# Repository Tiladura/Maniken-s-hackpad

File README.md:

# 6-KEY HACKPAD WITH ENGRAVINGS OF MY CATS NAME
## 2x3 hackpad which can be useful for creating macros or shortcuts for personal use. Convinient key placement, cute cat ascii images and my cats name are engraved(cats name - Tila).
## Features:
- 6 keys 2x3 placement
- xiao rp2040 microcontroller
### Here are my PCB images
| **Schematic** | **PCB** |
|---------------|---------|
||

dont ask why ground output is all the way down there. I don't know

## CAD

Hope you like the simple design! Added ascii cat images and my cats name onto the case :D

## Firmware
You can find firmware files in repo. Compiled it using QMK. To be honest it was such pain in the ass, but it seems to work xd
## Notes
Really liked doing the pcb and cad design! It was really satisfying
## BOM
- 1 SEEEDUINO XIAO RP2040
- 6x DSA Keycaps
- 4x M3x16 Bolt
- 4x M3 Heatset
- 1x case(2 printed parts)

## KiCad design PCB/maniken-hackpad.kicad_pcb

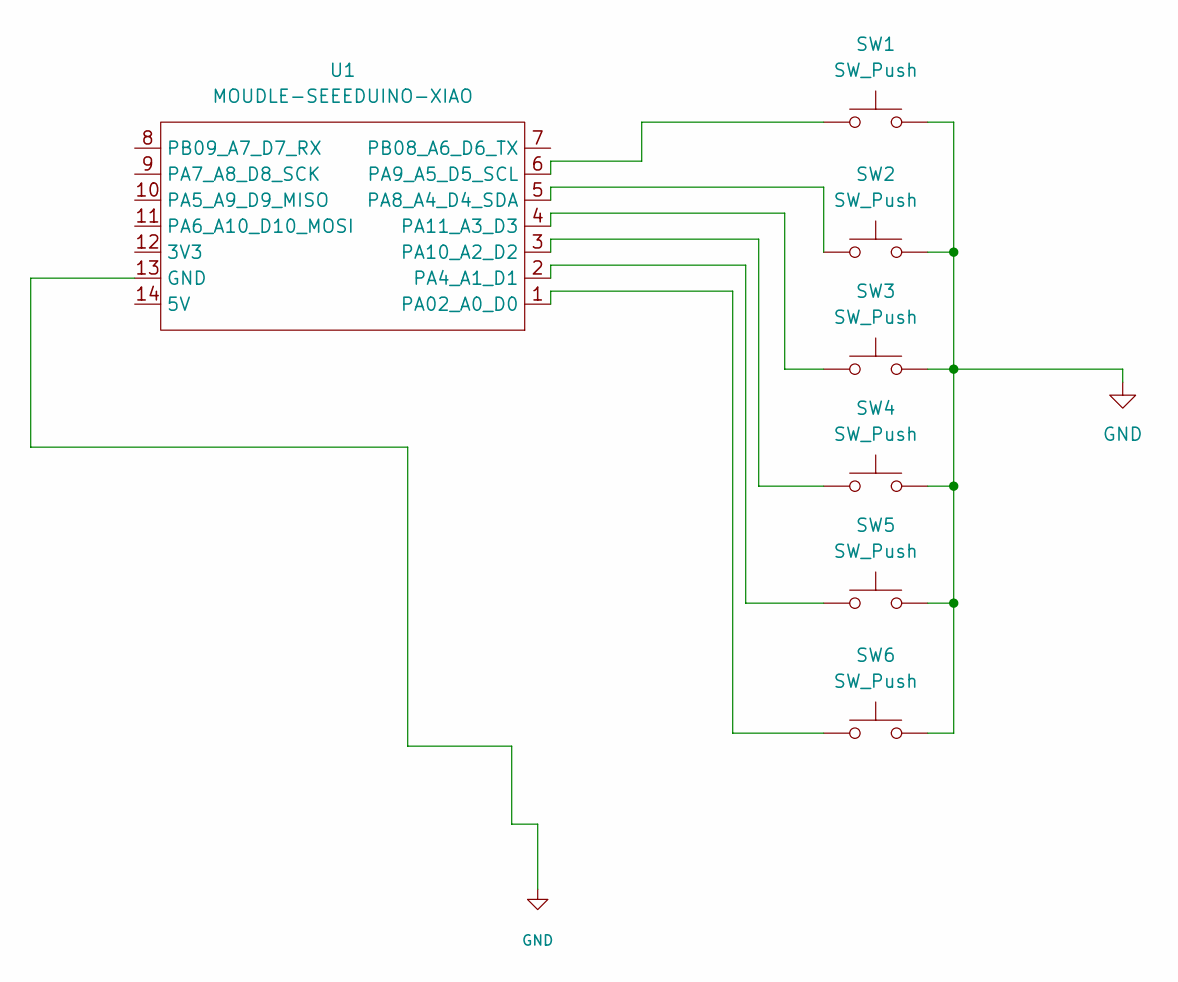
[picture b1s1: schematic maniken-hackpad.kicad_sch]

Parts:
SW1, SW2, SW3, SW4, SW5, SW6: SW_Push; SW_Cherry_MX_1.00u_PCB
U1: MOUDLE-SEEEDUINO-XIAO

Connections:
GND: SW1.2, SW2.2, SW3.2, SW4.2, SW5.2, SW6.2, U1.13 (GND)
unnamed: SW6.1, U1.1 (PA02_A0_D0)
unnamed: SW5.1, U1.2 (PA4_A1_D1)
unnamed: SW2.1, U1.5 (PA8_A4_D4_SDA)
unnamed: SW1.1, U1.6 (PA9_A5_D5_SCL)
unnamed: SW4.1, U1.3 (PA10_A2_D2)
unnamed: SW3.1, U1.4 (PA11_A3_D3)

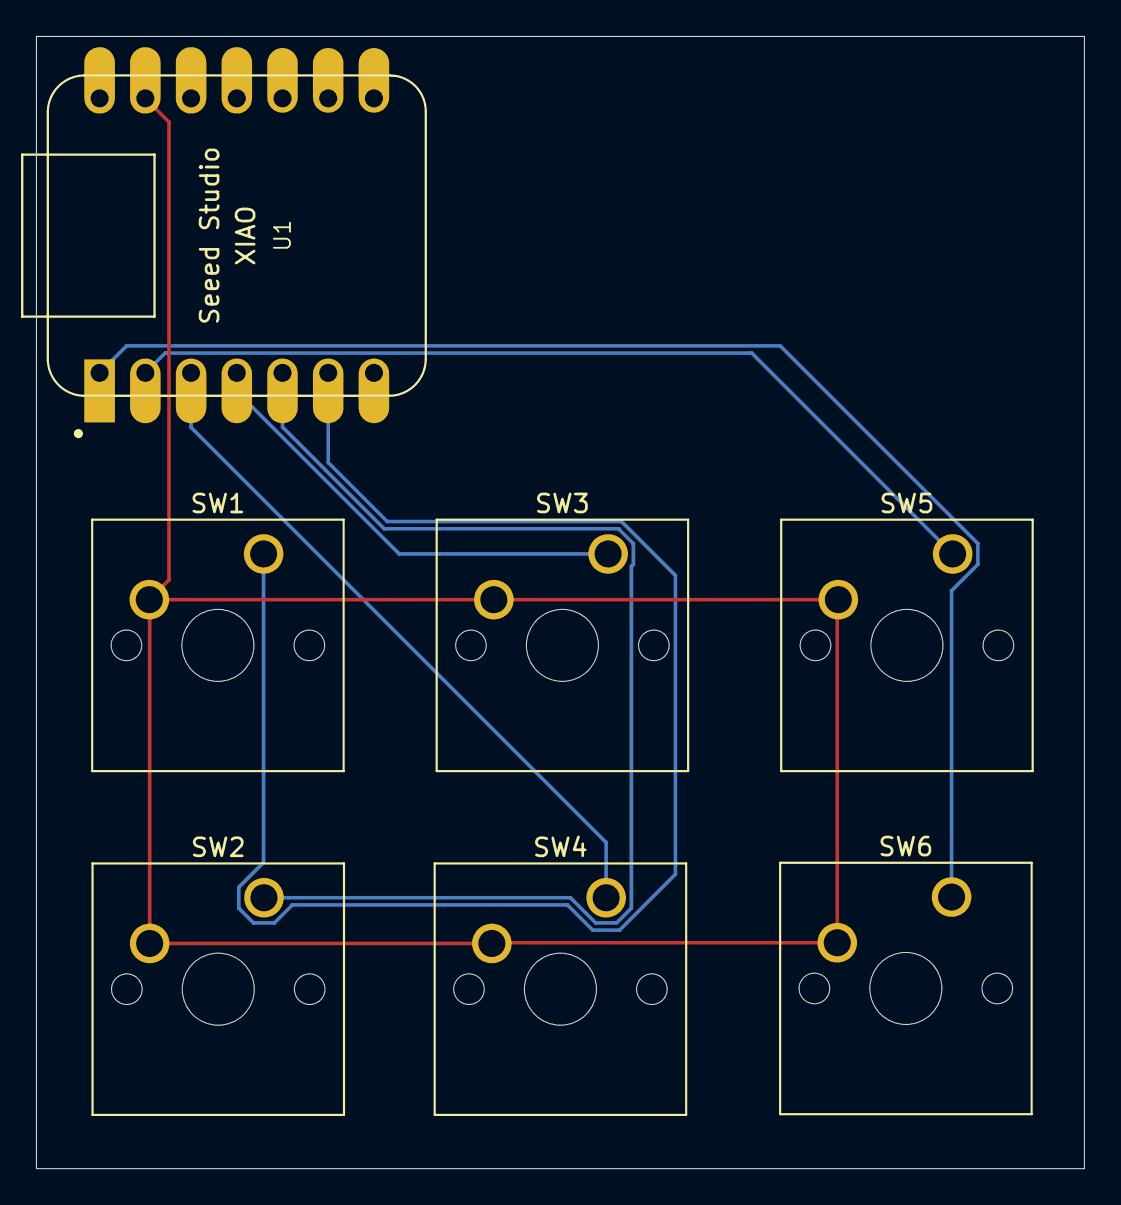
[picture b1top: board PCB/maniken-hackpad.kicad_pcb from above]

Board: 2 copper layers, 58.2 x 62.9 mm, 7 parts (0 on the bottom side), 7 nets.

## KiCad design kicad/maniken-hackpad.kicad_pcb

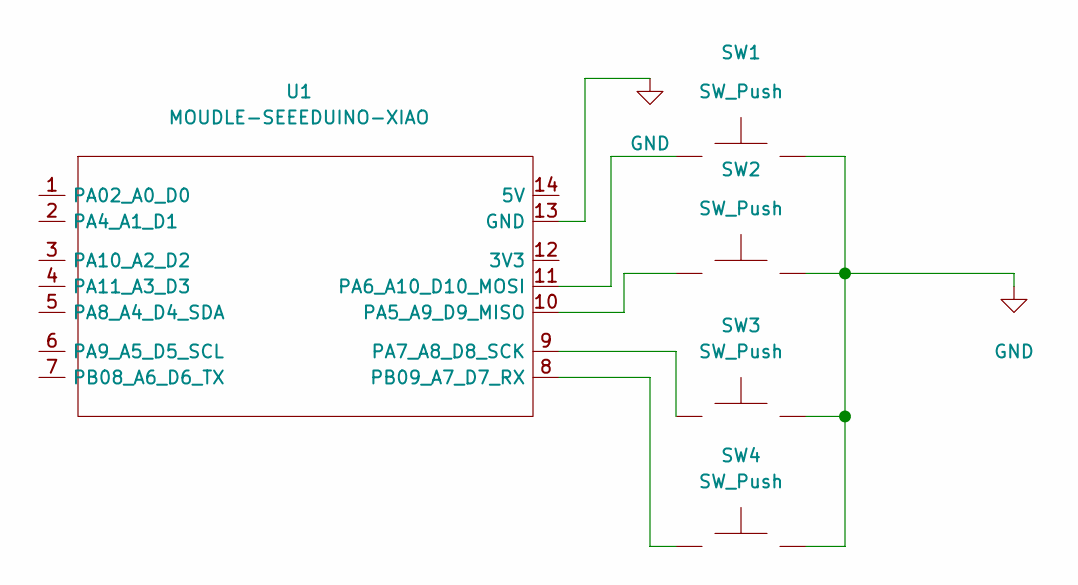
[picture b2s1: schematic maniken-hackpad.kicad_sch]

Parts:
SW1, SW2, SW3, SW4: SW_Push; SW_Cherry_MX_1.00u_PCB
U1: MOUDLE-SEEEDUINO-XIAO; XIAO-Generic-Hybrid-14P-2.54-21X17.8MM

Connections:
GND: SW1.2, SW2.2, SW3.2, SW4.2, U1.13 (GND)
unnamed: SW2.1, U1.10 (PA5_A9_D9_MISO)
unnamed: SW1.1, U1.11 (PA6_A10_D10_MOSI)
unnamed: SW3.1, U1.9 (PA7_A8_D8_SCK)
unnamed: SW4.1, U1.8 (PB09_A7_D7_RX)

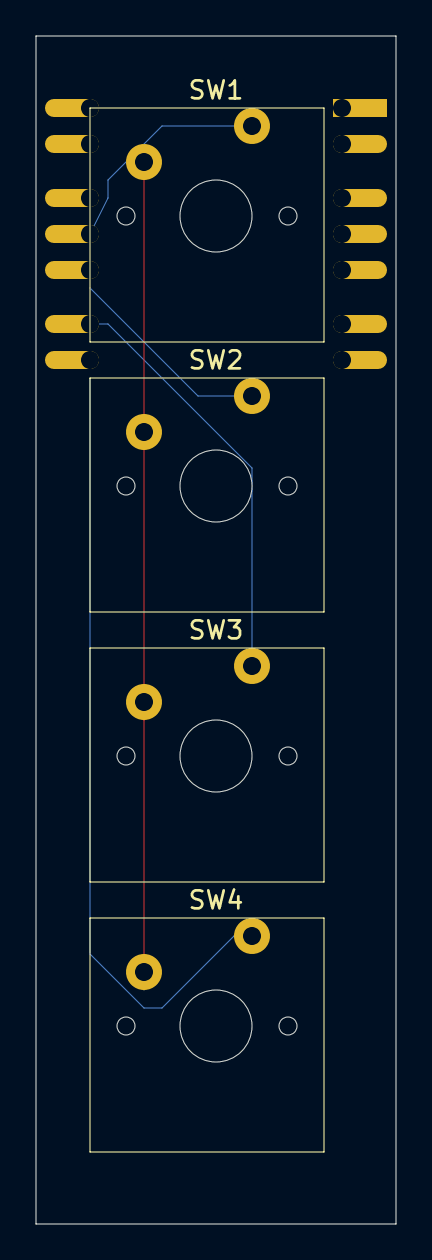
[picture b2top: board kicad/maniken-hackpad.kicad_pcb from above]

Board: 2 copper layers, 20.0 x 66.0 mm, 5 parts (1 on the bottom side), 5 nets.

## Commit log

2026-03-13 Create temp
2026-03-20 Create kicad
2026-03-20 Added CAD model of the hackpad
2026-03-20 README added
    Added project details and resources for the hackpad.
